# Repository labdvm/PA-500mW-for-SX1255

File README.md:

# PA-500mW-for-SX1255
500mW PA for SX1255 with TQP7M9106

# This PA you can use with SX1255 boards only without other PA's in the middle, dedicated for SXCEIVER and any other SX1255 boards without PA on it !!!
- This PA should be amplify ~400 mW clean Tetra signal.
# Board thickness is 0.8mm
- The L2,L3,L4 must be "wirewound" for better Q factor.
- The capacitors from the 100pF and below must be with 1% tolerance or better.
- The heatsink and cooler fan are mandatory !

Z32IT

You can order from here:

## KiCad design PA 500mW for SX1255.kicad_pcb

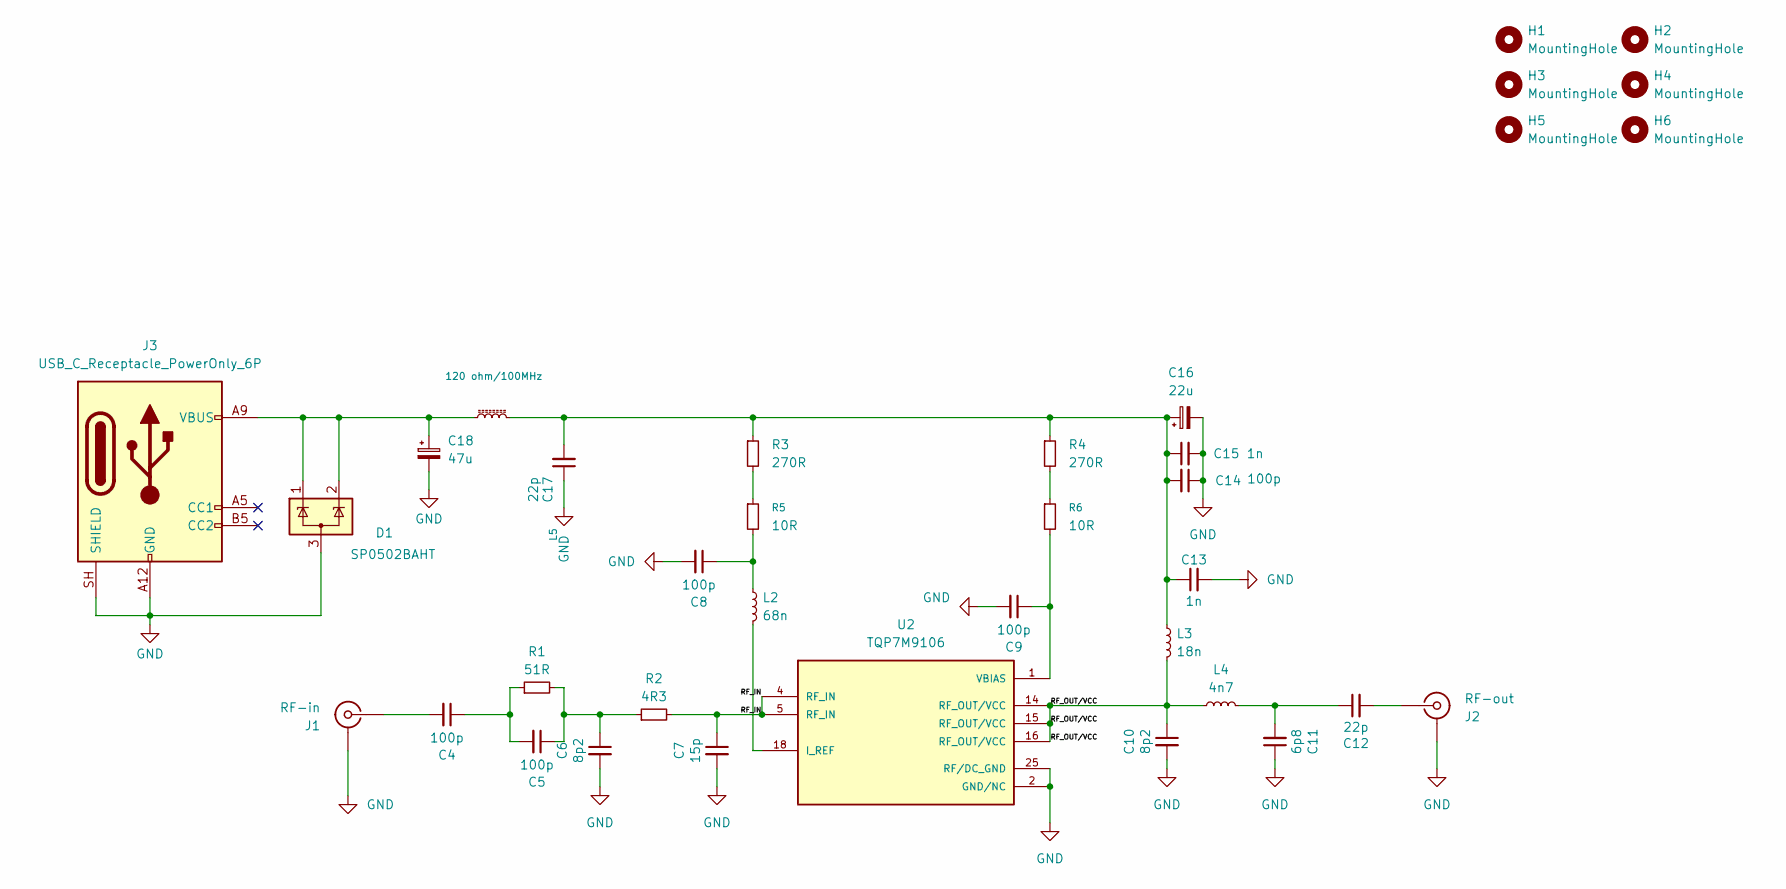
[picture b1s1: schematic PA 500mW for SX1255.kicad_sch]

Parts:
C4, C5, C8, C9, C14: 100p; C_0603_1608Metric; DigiKey Part Number 311-3599-1-ND
C6, C10: 8p2; C_0603_1608Metric; DigiKey Part Number 311-3347-1-ND
C7: 15p; C_0603_1608Metric; DigiKey Part Number 13-AC0603FRNPO9BN150CT-ND
C11: 6p8; C_0603_1608Metric; DigiKey Part Number 311-3838-1-ND
C12: 22p; C_0603_1608Metric; DigiKey Part Number 311-3350-1-ND
C13, C15: 1n; C_0603_1608Metric; DigiKey Part Number 490-1451-1-ND
C16: 22u; CP_EIA-3216-18_Kemet-A; DigiKey Part Number 478-1663-1-ND
C17: 22p; C_0805_2012Metric; DigiKey Part Number 311-4171-1-ND
C18: 47u; CP_EIA-3216-18_Kemet-A; DigiKey Part Number 478-8223-1-ND
D1: SP0502BAHT; SOT-23-3; DigiKey Part Number F2714CT-ND
H1, H2, H3, H4, H5, H6: MountingHole; MountingHole_2.2mm_M2_DIN965_Pad
J1: RF-in; SMA_Amphenol_132289_EdgeMount
J2: RF-out; SMA_Amphenol_132289_EdgeMount
J3: USB_C_Receptacle_PowerOnly_6P; USB_C_Receptacle_GCT_USB4125-xx-x_6P_TopMnt_Horizontal; DigiKey Part Number 6652-TYPE-C6PTR-ND
L2: 68n; L_0603_1608Metric; DigiKey Part Number 490-15846-1-ND
L3: 18n; L_1008_2520Metric; DigiKey Part Number 535-AISC-1008HQ-18NG-TTR-ND
L4: 4n7; L_0603_1608Metric; DigiKey Part Number 490-LQW18AS4N7J00DCT-ND
L5: 120 ohm/100MHz; L_1206_3216Metric; DigiKey Part Number 240-2401-1-ND
R1: 51R; R_0603_1608Metric; DigiKey Part Number 541-51.0HCT-ND
R2: 4R3; R_0603_1608Metric; DigiKey Part Number 541-4.30HHCT-ND
R3, R4: 270R; R_0603_1608Metric; DigiKey Part Number 541-5301-1-ND
R5, R6: 10R; R_0603_1608Metric; DigiKey Part Number 541-10.0HCT-ND
U2: TQP7M9106; QFN50P400X400X90-25N; DigiKey Part Number 2312-TQP7M9106CT-ND

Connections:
/RF_IN: C7.1, R2.2, U2.4 (RF_IN), U2.5 (RF_IN)
/RF_OUT/VCC: C10.1, L3.2, L4.1, U2.14 (RF_OUT/VCC), U2.15 (RF_OUT/VCC), U2.16 (RF_OUT/VCC)
GND: C6.2, C7.2, C8.2, C9.2, C10.2, C11.1, C13.2, C14.1, C15.2, C16.2, C17.1, C18.2, D1.3 (A), J1.2 (Ext), J2.2 (Ext), J3.A12 (GND), J3.B12 (GND), J3.SH (SHIELD), U2.2 (GND/NC), U2.3 (GND/NC), U2.6 (GND/NC), U2.7 (GND/NC), U2.8 (GND/NC), U2.9 (GND/NC), U2.10 (GND/NC), U2.11 (GND/NC), U2.12 (GND/NC), U2.13 (GND/NC), U2.17 (GND/NC), U2.19 (GND/NC), U2.20 (GND/NC), U2.21 (GND/NC), U2.22 (GND/NC), U2.23 (GND/NC), U2.24 (GND/NC), U2.25 (RF/DC_GND), U2.26 (RF/DC_GND)
unnamed: C4.1, C5.2, R1.1
unnamed: C5.1, C6.1, R1.2, R2.1
unnamed: C8.1, L2.1, R5.2
unnamed: C11.2, C12.1, L4.2
unnamed: C13.1, C14.2, C15.1, C16.1, C17.2, L3.1, L5.2, R3.1, R4.1
unnamed: C18.1, D1.1 (K), D1.2 (K), J3.A9 (VBUS), J3.B9 (VBUS), L5.1
unnamed: C4.2, J1.1 (In)
unnamed: C12.2, J2.1 (In)
unnamed: R3.2, R5.1
unnamed: R4.2, R6.1
unnamed: L2.2, U2.18 (I_REF)
unnamed: C9.1, R6.2, U2.1 (VBIAS)

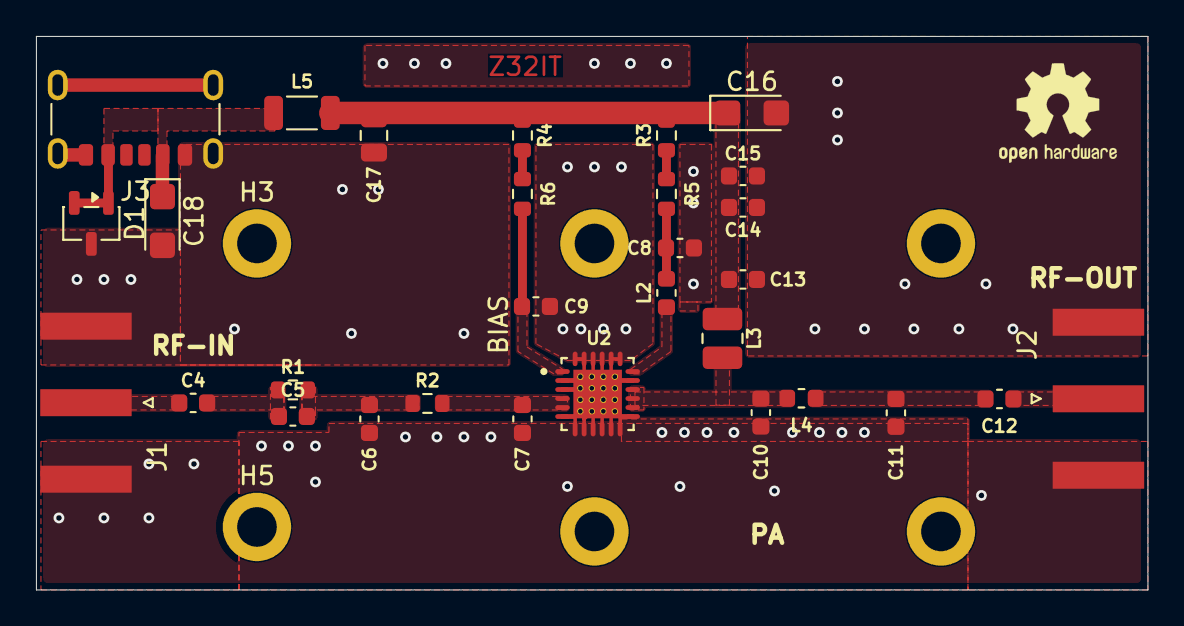
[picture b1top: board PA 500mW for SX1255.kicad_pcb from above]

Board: 2 copper layers, 61.8 x 30.8 mm, 36 parts (0 on the bottom side), 15 nets.

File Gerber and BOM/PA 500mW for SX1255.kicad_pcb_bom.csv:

Designator,Quantity,Value,Footprint,Package,MPN,DNP,Mount_Type,Description,Manufacturer,Manufacturer Product Number,DigiKey Part Number,KiLib_Generator,Q min,Current,Value2
"C10, C6",2,8p2,C_0603_1608Metric,,,,smt,"Unpolarized capacitor, small symbol",YAGEO,CC0603BRNPO9BN8R2,311-3347-1-ND,,,,
C11,1,6p8,C_0603_1608Metric,,,,smt,"Unpolarized capacitor, small symbol",YAGEO,CC0603BRNPO9BN6R8,311-3838-1-ND,,,,
C12,1,22p,C_0603_1608Metric,,,,smt,"Unpolarized capacitor, small symbol",YAGEO,CC0603FRNPO9BN220,311-3350-1-ND,,,,
"C13, C15",2,1n,C_0603_1608Metric,,,,smt,"Unpolarized capacitor, small symbol",Murata Electronics,GRM1885C1H102JA01D,490-1451-1-ND,,,,
"C14, C4, C5, C8, C9",5,100p,C_0603_1608Metric,,,,smt,,YAGEO,CC0603FRNPO9BN101,311-3599-1-ND,,,,
C16,1,22u,CP_EIA-3216-18_Kemet-A,,,,smt,"Polarized capacitor, small symbol",KYOCERA AVX,TAJA226K010RNJ,478-1663-1-ND,SMD_2terminal_chip_molded,,,
C17,1,22p,C_0805_2012Metric,,,,smt,,YAGEO,CC0805FRNPO9BN220,311-4171-1-ND,,,,
C18,1,47u,CP_EIA-3216-18_Kemet-A,,,,smt,"Polarized capacitor, small symbol",KYOCERA AVX,F931A476KAA,478-8223-1-ND,SMD_2terminal_chip_molded,,,
C7,1,15p,C_0603_1608Metric,,,,smt,"Unpolarized capacitor, small symbol",YAGEO,AC0603FRNPO9BN150,13-AC0603FRNPO9BN150CT-ND,,,,
D1,1,SP0502BAHT,SOT-23-3,,,,smt,"TVS Diode Array, 5.5V Standoff, 2 Channels, SOT-23 package",Littelfuse Inc.,SP0502BAHTG,F2714CT-ND,package/gullwing,,,
J3,1,USB_C_Receptacle_PowerOnly_6P,USB_C_Receptacle_GCT_USB4125-xx-x_6P_TopMnt_Horizontal,,,,smt,USB Power-Only 6P Type-C Receptacle connector,"Shenzhen SHOUHAN Technology Co., Ltd",TYPE-C 6P,6652-TYPE-C6PTR-ND,,,,
L2,1,68n,L_0603_1608Metric,,,,smt,"Inductor, small symbol",Murata Electronics,LQW18AS68NG0ZD,490-15846-1-ND,,49.3,600 mA,
L3,1,18n,L_1008_2520Metric,,,,smt,"Inductor, small symbol",Abracon LLC,AISC-1008HQ-18NG-T,535-AISC-1008HQ-18NG-TTR-ND,,62 @ 350 MHz,,
L4,1,4n7,L_0603_1608Metric,,,,smt,"Inductor, small symbol",Murata Electronics,LQW18AS4N7J00D,490-LQW18AS4N7J00DCT-ND,,,,
L5,1,120 ohm/100MHz,L_1206_3216Metric,,,,smt,"Inductor with ferrite core, small symbol",Laird-Signal Integrity Products,LI1206H121R-10,240-2401-1-ND,,,,120 ohm/100MHz 1000mA
R1,1,51R,R_0603_1608Metric,,,,smt,"Resistor, small symbol",Vishay Dale,CRCW060351R0FKEA,541-51.0HCT-ND,,,,
R2,1,4R3,R_0603_1608Metric,,,,smt,"Resistor, small symbol",Vishay Dale,CRCW06034R30FKEA,541-4.30HHCT-ND,,,,
"R3, R4",2,270R,R_0603_1608Metric,,,,smt,"Resistor, small symbol",Vishay Dale,CRCW0603270RFKEAC,541-5301-1-ND,,,,
"R5, R6",2,10R,R_0603_1608Metric,,,,smt,"Resistor, small symbol",Vishay Dale,CRCW060310R0FKEA,541-10.0HCT-ND,SMD_2terminal_chip_molded,,,
U2,1,TQP7M9106,QFN50P400X400X90-25N,,,,smt,,Qorvo,TQP7M9106,2312-TQP7M9106CT-ND,,,,

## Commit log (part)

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2026-06-20 Update README with amplification details
    Added information about the PA's amplification capabilities.
2026-06-20 Update README with board thickness detail
    Added board thickness information to README.
